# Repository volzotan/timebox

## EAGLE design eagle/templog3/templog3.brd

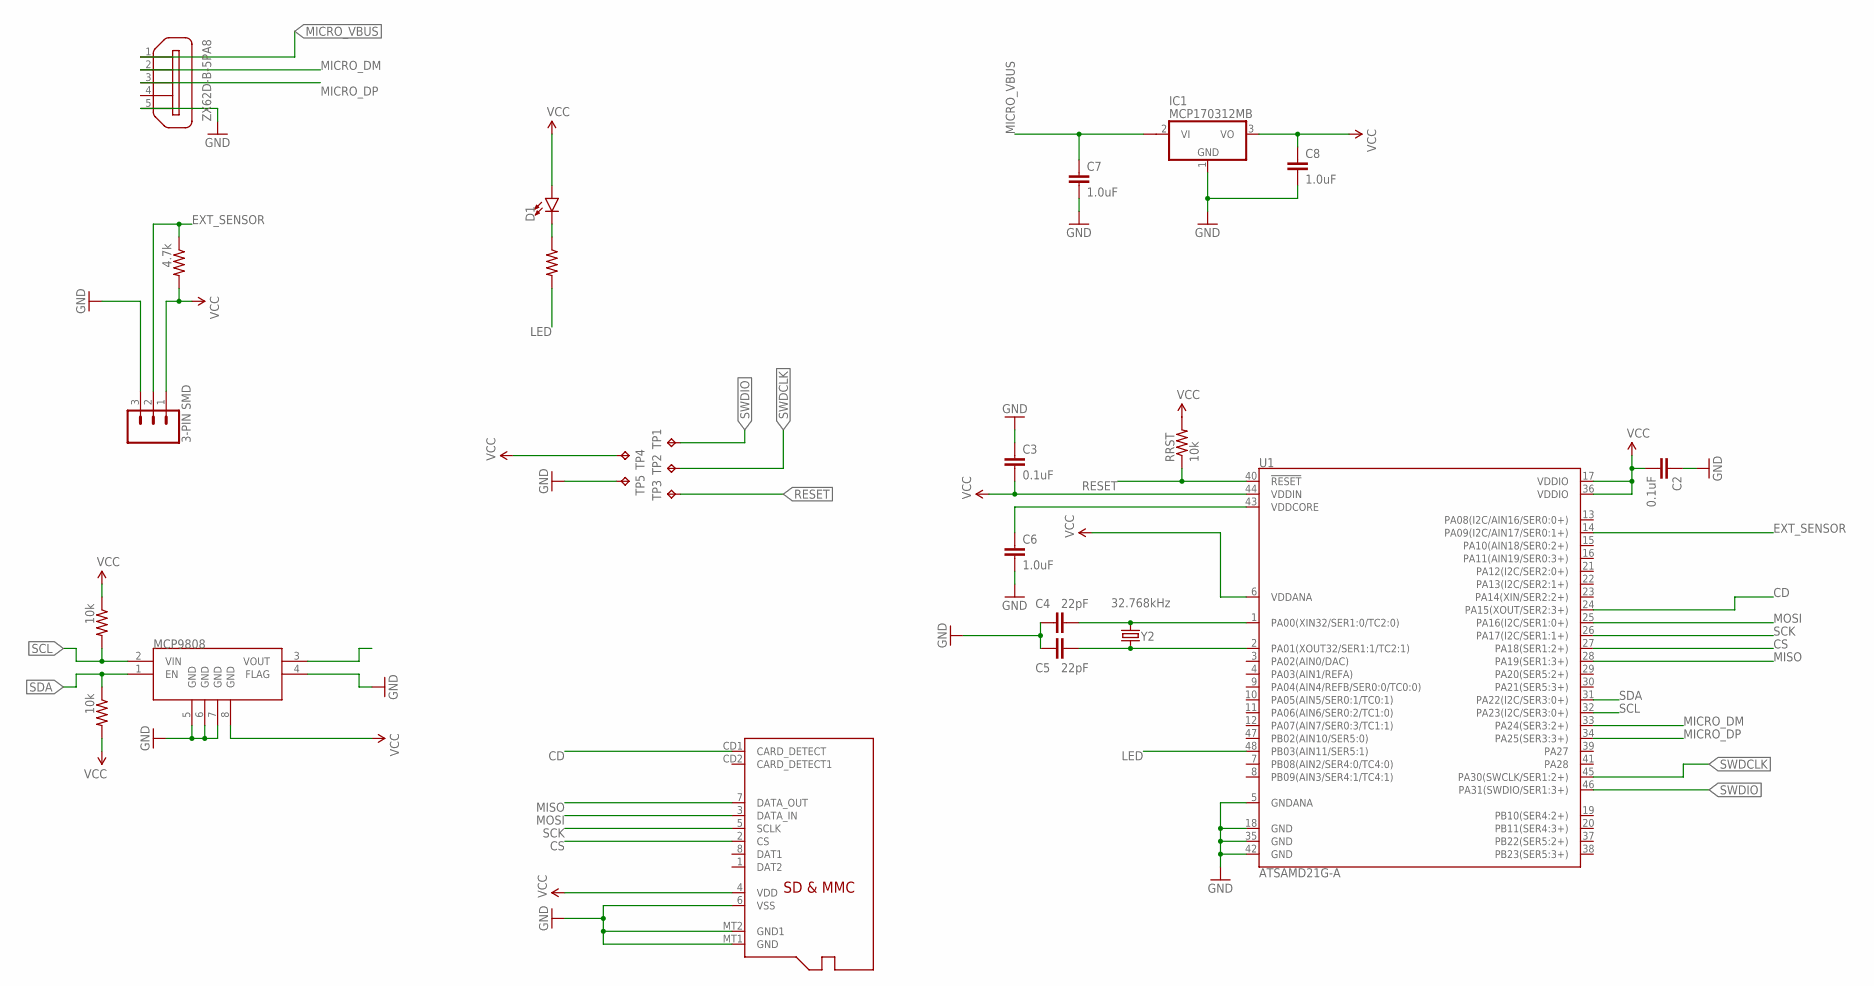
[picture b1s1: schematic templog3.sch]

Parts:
C2, C3: 0.1uF; 0805
C4, C5: 22pF; 0805
C6, C7, C8: 1.0uF; 0805
D1: LED1206; LED-1206
IC1: MCP170312MB; SOT89
J2: 3-PIN SMD; JST-3-SMD
MCP9808: V_REG_MIC5216; MSOP8
RRST: 10k; 0805
R_I2C_1, R_I2C_2: 10k; 0805
R_I2C_3: 4.7k; 0805
R_I2C_4: RESISTOR0805-RES; 0805
TP1, TP2, TP3, TP4, TP5: TPB1,27; B1,27
U1: ATSAMD21G-A; TQFP-48
U$1: MICROSD
X2: ZX62D-B-5PA8
Y2: 32.768kHz; CRYSTAL-SMD-3.2X1.5MM

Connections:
CD: U1.24 (PA15(XOUT/SER2:3+)), U$1.CD1 (CARD_DETECT)
CS: U1.27 (PA18(SER1:2+)), U$1.2 (CS)
EXT_SENSOR: J2.2, R_I2C_3.1, U1.14 (PA09(I2C/AIN17/SER0:1+))
GND: C2.1, C3.1, C4.1, C5.1, C6.2, C7.2, C8.2, IC1.1 (GND), J2.3, MCP9808.4 (FLAG), MCP9808.5 (GND), MCP9808.6 (GND), MCP9808.7 (GND), TP5.TP, U1.5 (GNDANA), U1.18 (GND), U1.35 (GND), U1.42 (GND), U$1.6 (VSS), U$1.MT1 (GND), U$1.MT2 (GND1), X2.5
LED: R_I2C_4.2, U1.48 (PB03(AIN11/SER5:1))
MICRO_DM: U1.33 (PA24(SER3:2+)), X2.2
MICRO_DP: U1.34 (PA25(SER3:3+)), X2.3
MICRO_VBUS: C7.1, IC1.2@1 (VI1), X2.1
MISO: U1.28 (PA19(SER1:3+)), U$1.7 (DATA_OUT)
MOSI: U1.25 (PA16(I2C/SER1:0+)), U$1.3 (DATA_IN)
unnamed: C6.1, U1.43 (VDDCORE)
unnamed: D1.C, R_I2C_4.1
unnamed: C4.2, U1.1 (PA00(XIN32/SER1:0/TC2:0)), Y2.P$2 (2)
unnamed: C5.2, U1.2 (PA01(XOUT32/SER1:1/TC2:1)), Y2.P$1 (1)
RESET: RRST.1, TP3.TP, U1.40 (!RESET!)
SCK: U1.26 (PA17(I2C/SER1:1+)), U$1.5 (SCLK)
SCL: MCP9808.2 (VIN), R_I2C_1.2, U1.32 (PA23(I2C/SER3:0+))
SDA: MCP9808.1 (EN), R_I2C_2.1, U1.31 (PA22(I2C/SER3:0+))
SWDCLK: TP2.TP, U1.45 (PA30(SWCLK/SER1:2+))
SWDIO: TP1.TP, U1.46 (PA31(SWDIO/SER1:3+))
VCC: C2.2, C3.2, C8.1, D1.A, IC1.3 (VO), J2.1, MCP9808.8 (GND), RRST.2, R_I2C_1.1, R_I2C_2.2, R_I2C_3.2, TP4.TP, U1.6 (VDDANA), U1.17 (VDDIO), U1.36 (VDDIO), U1.44 (VDDIN), U$1.4 (VDD)

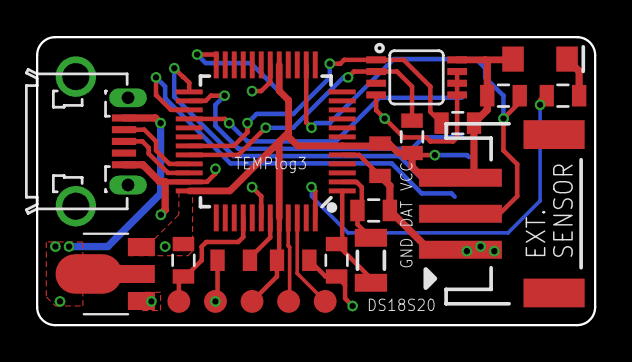
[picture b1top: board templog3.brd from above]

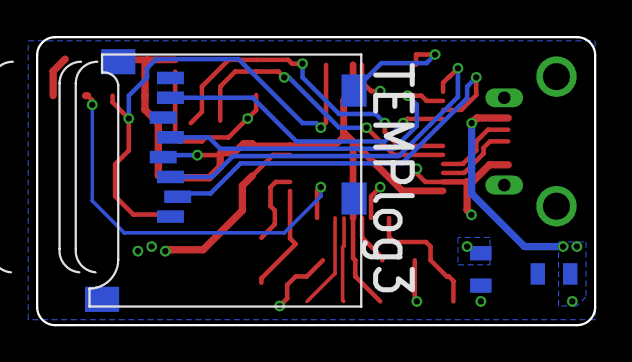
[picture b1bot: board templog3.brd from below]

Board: 2 copper layers, 31.0 x 16.0 mm, 25 parts (3 on the bottom side), 21 nets.

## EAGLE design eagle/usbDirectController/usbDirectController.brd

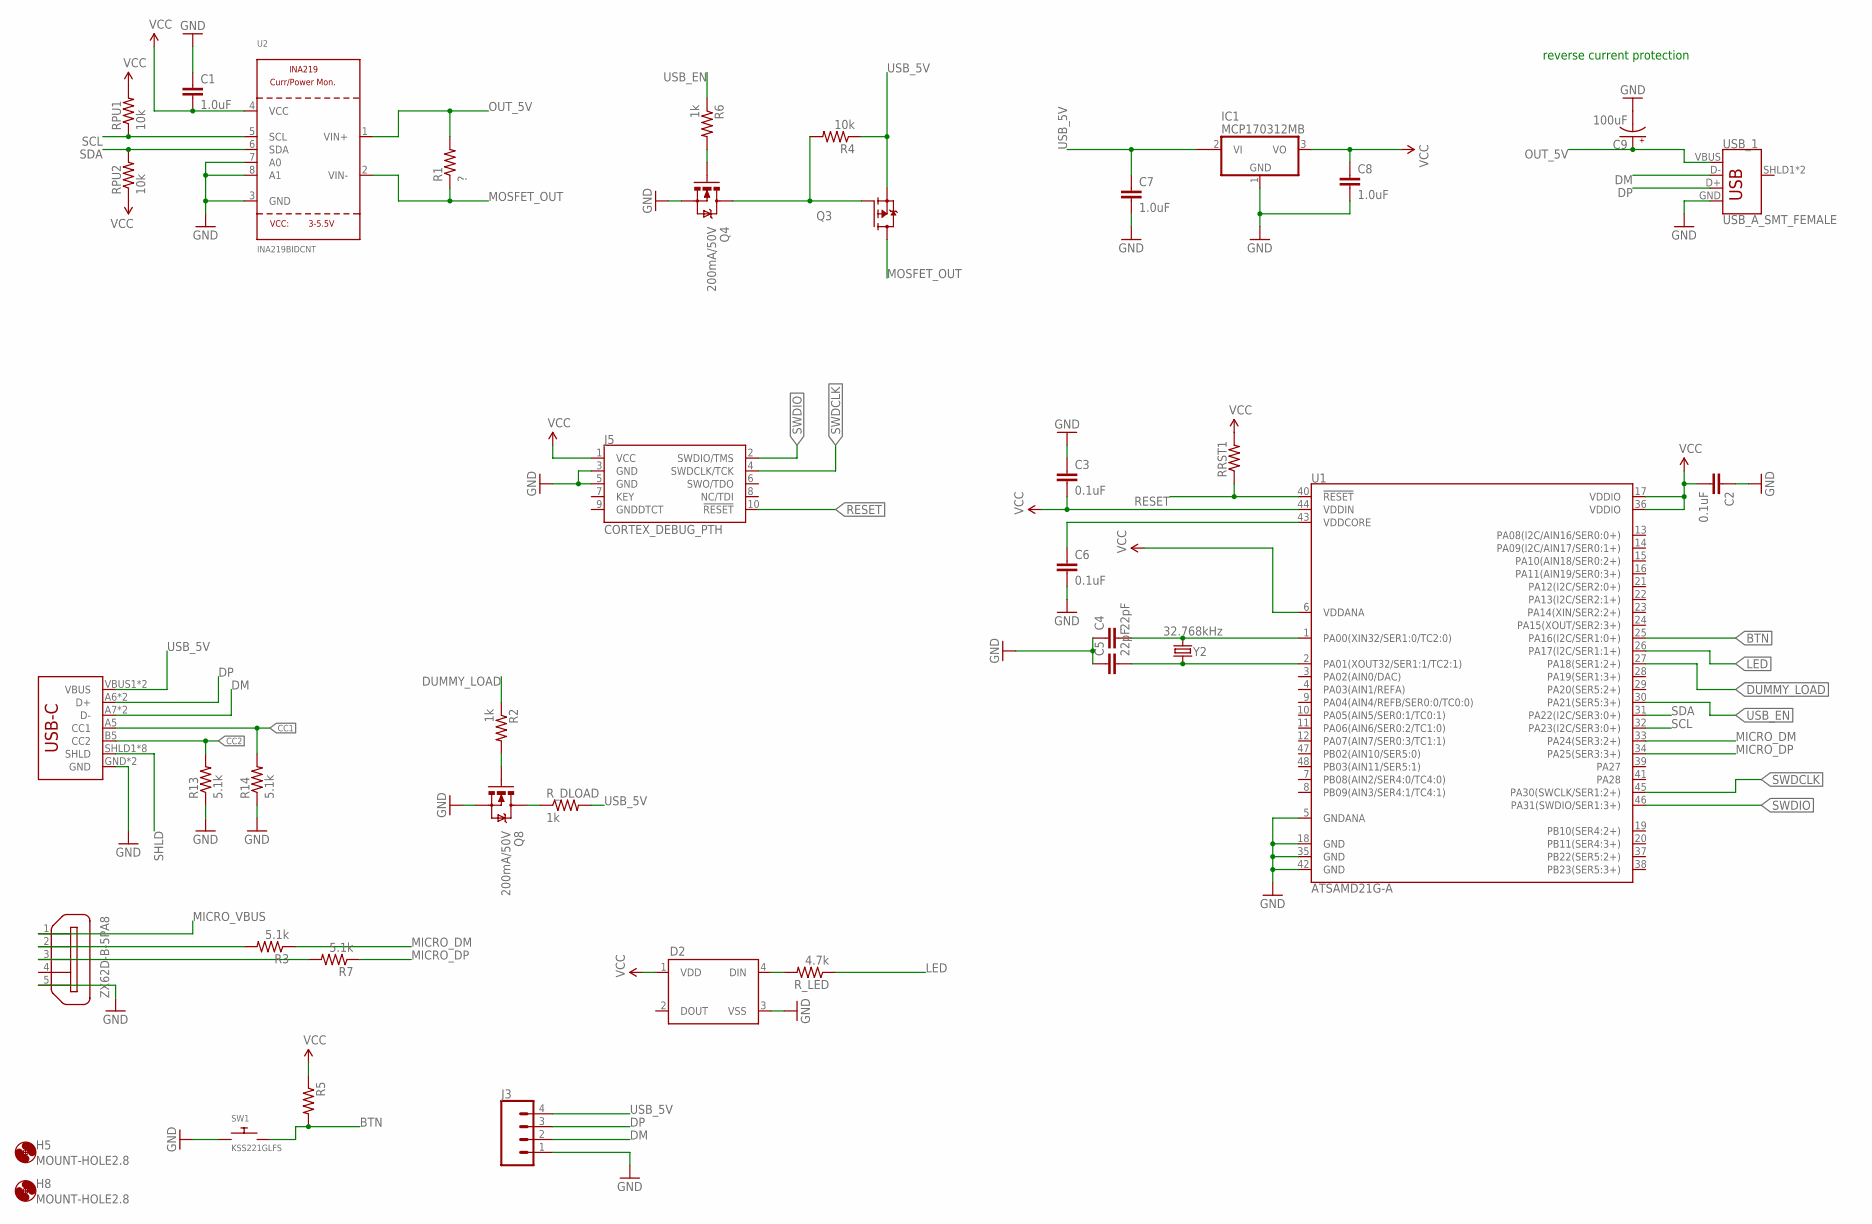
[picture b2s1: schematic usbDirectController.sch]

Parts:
C1, C7, C8: 1.0uF; 0805
C2, C3, C6: 0.1uF; 0805
C4, C5: 22pF; 0805
C9: 100uF; PANASONIC_D
D2: WS2812B
H5, H8: MOUNT-HOLE2.8; 2,8
IC1: MCP170312MB; SOT89
J1: USB_C16PIN; USB-C-16P
J3: CONN_04; 1X04
J5: CORTEX_DEBUG_PTH; 2X5-PTH-1.27MM
Q3: FDD4141TO252; TO252
Q4, Q8: 200mA/50V; SOT23-3
R1: ?; R2010
R2, R6: 1k; 0805
R3, R7, R13, R14: 5.1k; 0805
R4: 10k; 0805
R5: RESISTOR0805-RES; 0805
RPU1, RPU2: 10k; 0805
RRST1: RESISTOR0805-RES; 0805
R_DLOAD: 1k; 1206
R_LED: 4.7k; 0805
SW1: KSS221GLFS; BTN_CK_KSS
U1: ATSAMD21G-A; TQFP-48
U2: INA219BIDCNT; SOT23-8
USB_1: USB_A_SMT_FEMALE; USB-A-S-SILK-FEMALE
X2: ZX62D-B-5PA8
Y2: 32.768kHz; CRYSTAL-SMD-3.2X1.5MM

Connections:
BTN: R5.2, SW1.P$2, U1.25 (PA16(I2C/SER1:0+))
CC1: J1.A5 (CC1), R14.2
CC2: J1.B5 (CC2), R13.2
DM: J1.A7 (D-), J1.B7 (D-), J3.2, USB_1.D-
DP: J1.A6 (D+), J1.B6 (D+), J3.3, USB_1.D+
DUMMY_LOAD: R2.1, U1.27 (PA18(SER1:2+))
GND: C1.1, C2.1, C3.1, C4.1, C5.1, C6.2, C7.2, C8.2, C9.-, D2.3 (VSS), IC1.1 (GND), J1.GND, J1.GND2 (GND), J3.1, J5.3 (GND), J5.5 (GND), Q4.2 (S), Q8.2 (S), R13.1, R14.1, SW1.P$1, U1.5 (GNDANA), U1.18 (GND), U1.35 (GND), U1.42 (GND), U2.3 (GND), U2.7 (A0), U2.8 (A1), USB_1.GND, X2.5
LED: R_LED.1, U1.26 (PA17(I2C/SER1:1+))
MICRO_DM: R3.1, U1.33 (PA24(SER3:2+))
MICRO_DP: R7.1, U1.34 (PA25(SER3:3+))
MICRO_VBUS: X2.1
MOSFET_OUT: Q3.3 (D), R1.1, U2.2 (VIN-)
unnamed: C6.1, U1.43 (VDDCORE)
unnamed: Q4.1 (G), R6.2
unnamed: Q3.1 (G), Q4.3 (D), R4.2
unnamed: R3.2, X2.2
unnamed: D2.4 (DIN), R_LED.2
unnamed: C4.2, U1.1 (PA00(XIN32/SER1:0/TC2:0)), Y2.P$2 (2)
unnamed: R7.2, X2.3
unnamed: Q8.1 (G), R2.2
unnamed: Q8.3 (D), R_DLOAD.1
unnamed: C5.2, U1.2 (PA01(XOUT32/SER1:1/TC2:1)), Y2.P$1 (1)
OUT_5V: C9.+, R1.2, U2.1 (VIN+), USB_1.VBUS
RESET: J5.10 (!RESET), RRST1.1, U1.40 (!RESET!)
SCL: RPU1.1, U1.32 (PA23(I2C/SER3:0+)), U2.5 (SCL)
SDA: RPU2.2, U1.31 (PA22(I2C/SER3:0+)), U2.6 (SDA)
SHLD: J1.SHLD1 (SHLD), J1.SHLD2 (SHLD), J1.SHLD3 (SHLD), J1.SHLD4 (SHLD), J1.SHLD5 (SHLD), J1.SHLD6 (SHLD), J1.SHLD7 (SHLD), J1.SHLD8 (SHLD)
SWDCLK: J5.4 (SWDCLK/TCK), U1.45 (PA30(SWCLK/SER1:2+))
SWDIO: J5.2 (SWDIO/TMS), U1.46 (PA31(SWDIO/SER1:3+))
USB_5V: C7.1, IC1.2@1 (VI1), J1.VBUS1 (VBUS), J1.VBUS2 (VBUS), J3.4, Q3.2 (S), R4.1, R_DLOAD.2
USB_EN: R6.1, U1.30 (PA21(SER5:3+))
VCC: C1.2, C2.2, C3.2, C8.1, D2.1 (VDD), IC1.3 (VO), J5.1 (VCC), R5.1, RPU1.2, RPU2.1, RRST1.2, U1.6 (VDDANA), U1.17 (VDDIO), U1.36 (VDDIO), U1.44 (VDDIN), U2.4 (VCC)

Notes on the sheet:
reverse current protection

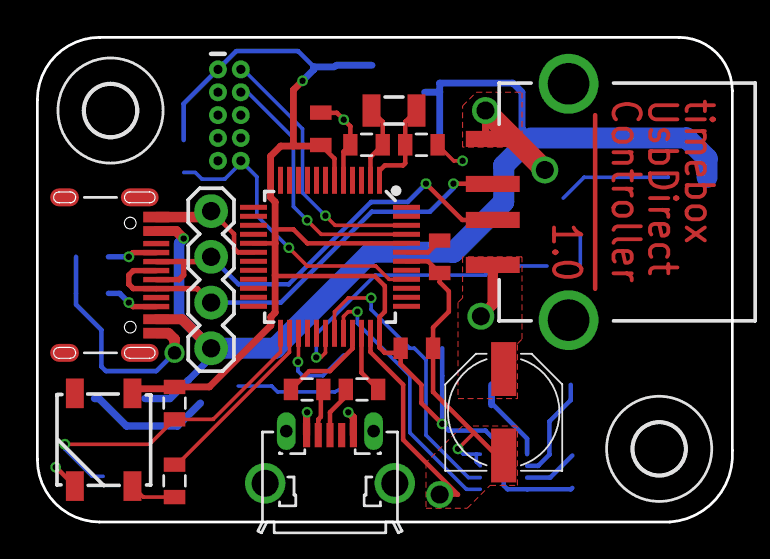
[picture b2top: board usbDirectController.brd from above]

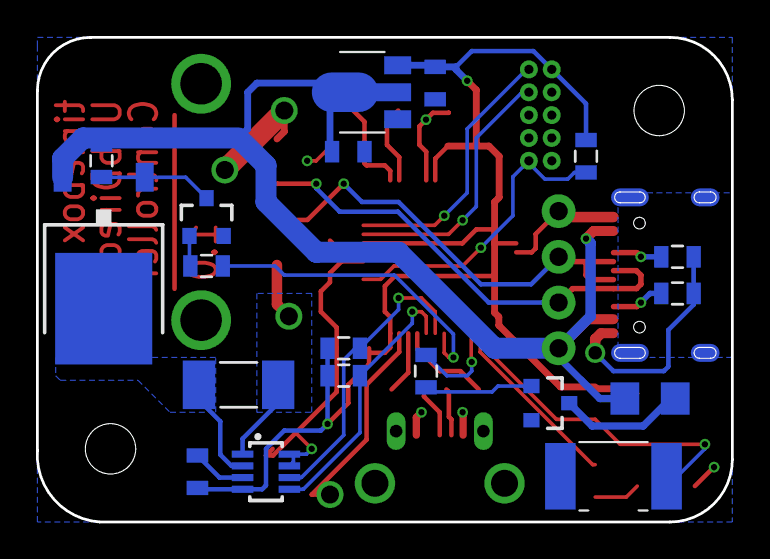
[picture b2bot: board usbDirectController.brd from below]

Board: 2 copper layers, 38.6 x 26.9 mm, 39 parts (19 on the bottom side), 31 nets.

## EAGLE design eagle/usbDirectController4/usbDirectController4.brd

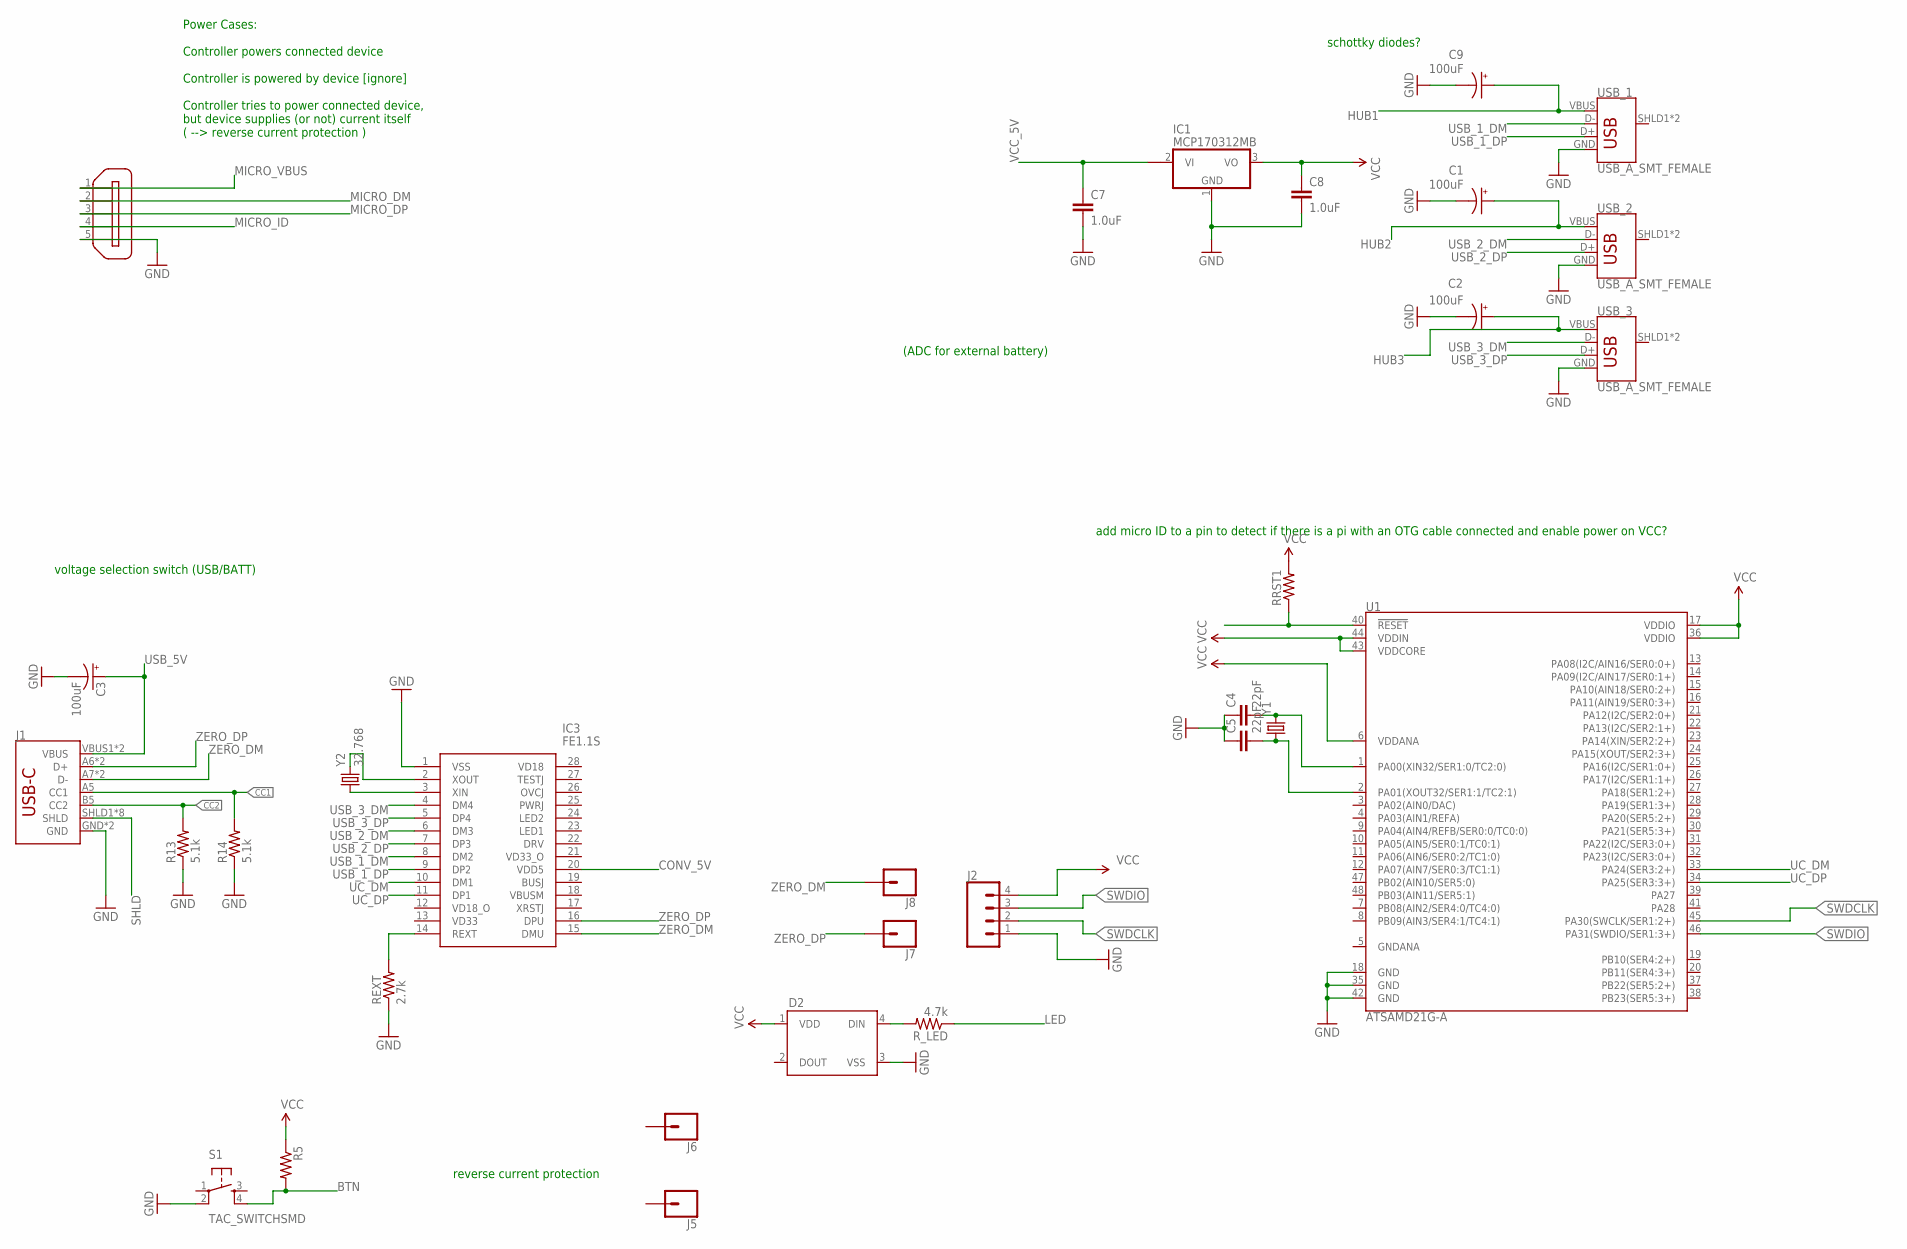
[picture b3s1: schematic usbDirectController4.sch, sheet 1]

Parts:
C1, C2, C3, C9: 100uF; PANASONIC_D
C4, C5: 22pF; 1206
C7, C8: 1.0uF; 1206
D2: WS2812B
IC1: MCP170312MB; SOT89
IC3: FE1.1S; SOP64P600X175-28N
J1: USB_C16PIN; USB-C-16P
J2: CONN_04; 1X04
J5, J6, J7, J8: CONN_01POGOPIN_HOLE_0.58; 1X01_POGOPIN_HOLE_0.58_DIA
R5: RESISTOR1206; 1206
R13, R14: 5.1k; 0805
REXT: 2.7k; 1206
RRST1: RESISTOR1206; 1206
R_LED: 4.7k; 1206
S1: TAC_SWITCHSMD; TACTILE-PTH
U1: ATSAMD21G-A; TQFP-48
USB_1, USB_2, USB_3: USB_A_SMT_FEMALE; USB-A-S-SILK-FEMALE
X2: ZX62D-B-5PA8
Y1: CRYSTALCRYSTAL-SMD-5X3-16MHZ; CRYSTAL-SMD-5X3
Y2: 32.768; CRYSTAL-SMD-5X3

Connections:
BTN: R5.2, S1.4
CC1: J1.A5 (CC1), R14.2
CC2: J1.B5 (CC2), R13.2
CONV_5V: IC3.20 (VDD5)
GND: C1.-, C2.-, C3.-, C4.1, C5.1, C7.2, C8.2, C9.-, D2.3 (VSS), IC1.1 (GND), IC3.1 (VSS), J1.GND, J1.GND2 (GND), J2.1, R13.1, R14.1, REXT.1, S1.2, U1.18 (GND), U1.35 (GND), U1.42 (GND), USB_1.GND, USB_2.GND, USB_3.GND, X2.5; also elsewhere on the board
HUB1: C9.+, USB_1.VBUS
HUB2: C1.+, USB_2.VBUS
HUB3: C2.+, USB_3.VBUS
LED: R_LED.1
MICRO_DM: X2.2
MICRO_DP: X2.3
MICRO_ID: X2.4
MICRO_VBUS: X2.1
unnamed: D2.4 (DIN), R_LED.2
unnamed: C4.2, U1.1 (PA00(XIN32/SER1:0/TC2:0)), Y1.3 (2)
unnamed: RRST1.1, U1.40 (!RESET!)
unnamed: IC3.3 (XIN), Y2.1
unnamed: IC3.2 (XOUT), Y2.3 (2)
unnamed: IC3.14 (REXT), REXT.2
unnamed: C5.2, U1.2 (PA01(XOUT32/SER1:1/TC2:1)), Y1.1
SHLD: J1.SHLD1 (SHLD), J1.SHLD2 (SHLD), J1.SHLD3 (SHLD), J1.SHLD4 (SHLD), J1.SHLD5 (SHLD), J1.SHLD6 (SHLD), J1.SHLD7 (SHLD), J1.SHLD8 (SHLD)
SWDCLK: J2.2, U1.45 (PA30(SWCLK/SER1:2+))
SWDIO: J2.3, U1.46 (PA31(SWDIO/SER1:3+))
UC_DM: IC3.10 (DM1), U1.33 (PA24(SER3:2+))
UC_DP: IC3.11 (DP1), U1.34 (PA25(SER3:3+))
USB_1_DM: IC3.8 (DM2), USB_1.D-
USB_1_DP: IC3.9 (DP2), USB_1.D+
USB_2_DM: IC3.6 (DM3), USB_2.D-
USB_2_DP: IC3.7 (DP3), USB_2.D+
USB_3_DM: IC3.4 (DM4), USB_3.D-
USB_3_DP: IC3.5 (DP4), USB_3.D+
USB_5V: C3.+, J1.VBUS1 (VBUS), J1.VBUS2 (VBUS)
VCC: C8.1, D2.1 (VDD), IC1.3 (VO), J2.4, R5.1, RRST1.2, U1.6 (VDDANA), U1.17 (VDDIO), U1.36 (VDDIO), U1.43 (VDDCORE), U1.44 (VDDIN)
VCC_5V: C7.1, IC1.2@1 (VI1); also elsewhere on the board
ZERO_DM: IC3.15 (DMU), J1.A7 (D-), J1.B7 (D-), J8.1
ZERO_DP: IC3.16 (DPU), J1.A6 (D+), J1.B6 (D+), J7.1

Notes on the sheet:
(ADC for external battery)
schottky diodes?
voltage selection switch (USB/BATT)
reverse current protection
add micro ID to a pin to detect if there is a pi with an OTG cable connected and enable power on VCC?
Power Cases: Controller powers connected device Controller is powered by device [ignore] Controller tries to power connected device, but device supplies (or not) current itself ( --> reverse current protection )

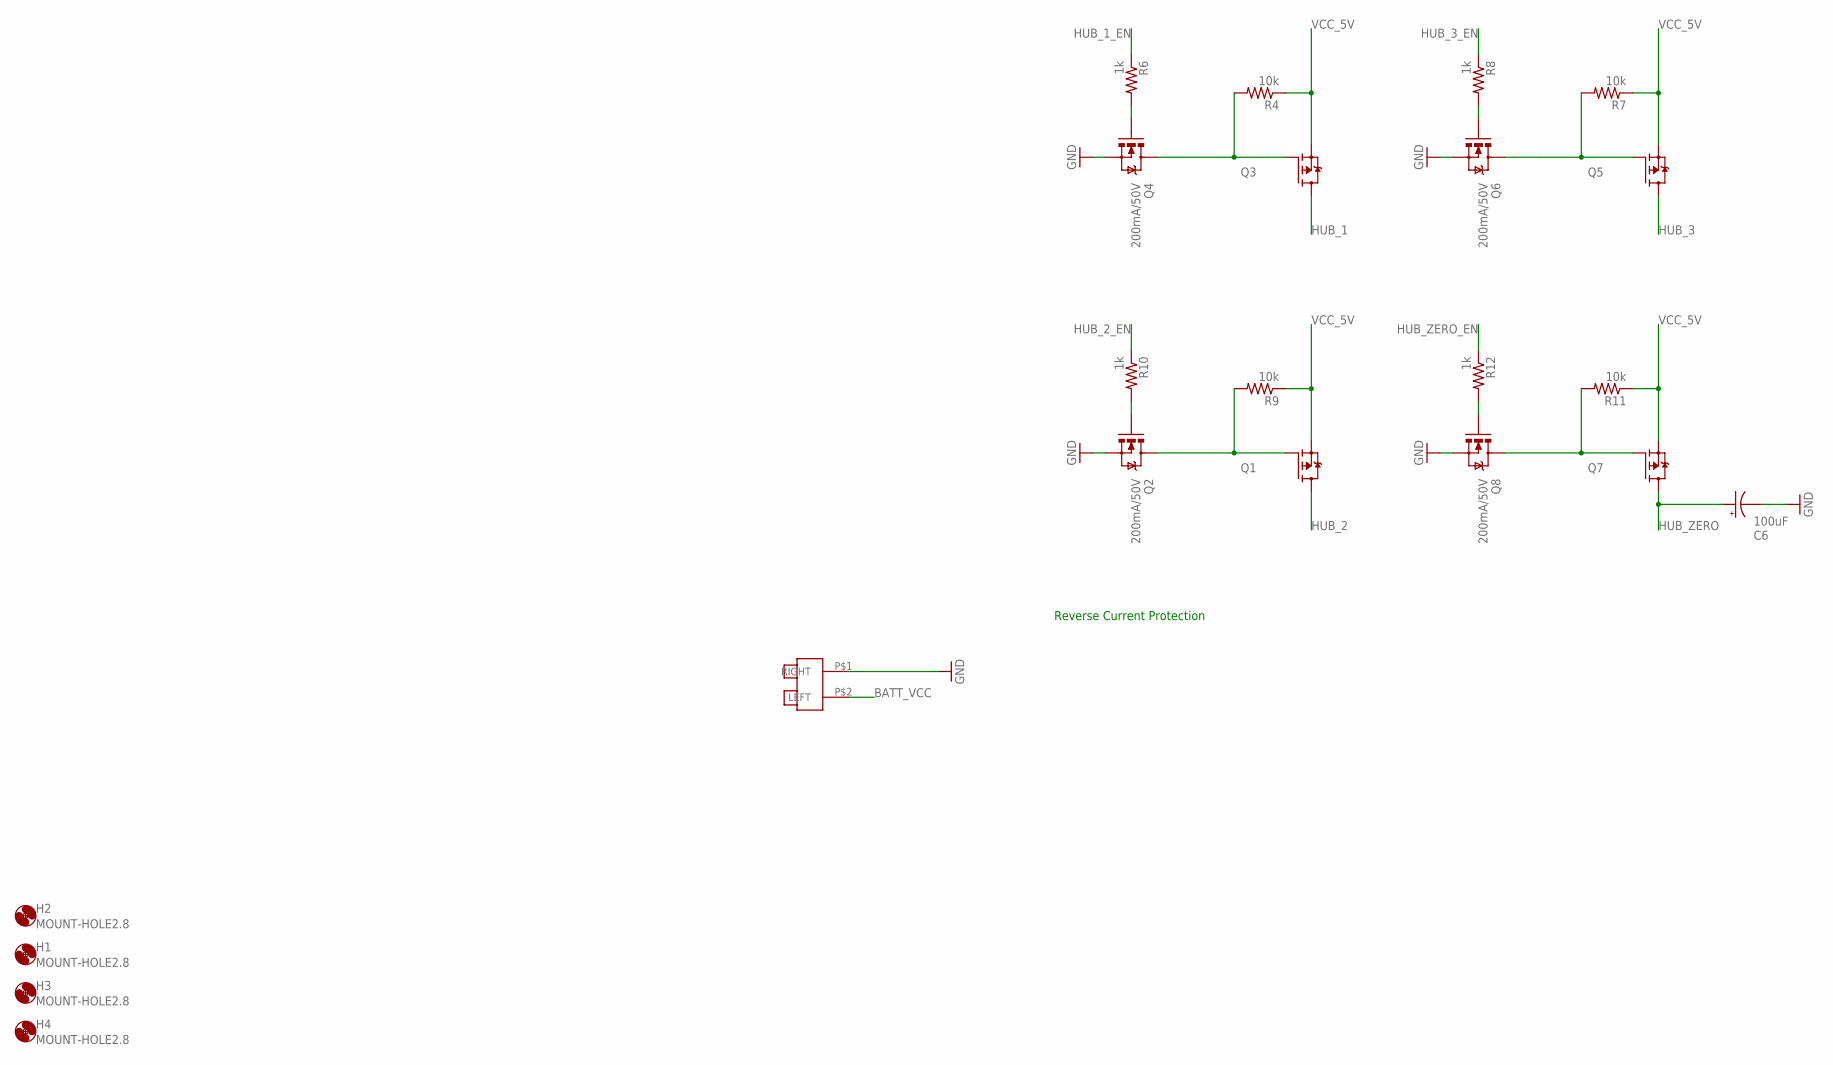
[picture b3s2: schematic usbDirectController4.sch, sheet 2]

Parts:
C6: 100uF; PANASONIC_D
H1, H2, H3, H4: MOUNT-HOLE2.8; 2,8
Q1, Q3, Q5, Q7: FDD4141TO252; TO252
Q2, Q4, Q6, Q8: 200mA/50V; SOT23-3
R4, R7, R9, R11: 10k; 1206
R6, R8, R10, R12: 1k; 1206
U$4: NANOFIT2

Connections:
BATT_VCC: U$4.P$2 (LEFT)
GND: C6.-, Q2.2 (S), Q4.2 (S), Q6.2 (S), Q8.2 (S), U$4.P$1 (RIGHT); also elsewhere on the board
HUB_1: Q3.3 (D)
HUB_1_EN: R6.1
HUB_2: Q1.3 (D)
HUB_2_EN: R10.1
HUB_3: Q5.3 (D)
HUB_3_EN: R8.1
HUB_ZERO: C6.+, Q7.3 (D)
HUB_ZERO_EN: R12.1
unnamed: Q1.1 (G), Q2.3 (D), R9.2
unnamed: Q4.1 (G), R6.2
unnamed: Q3.1 (G), Q4.3 (D), R4.2
unnamed: Q2.1 (G), R10.2
unnamed: Q5.1 (G), Q6.3 (D), R7.2
unnamed: Q6.1 (G), R8.2
unnamed: Q7.1 (G), Q8.3 (D), R11.2
unnamed: Q8.1 (G), R12.2
VCC_5V: Q1.2 (S), Q3.2 (S), Q5.2 (S), Q7.2 (S), R4.1, R7.1, R9.1, R11.1; also elsewhere on the board

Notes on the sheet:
Reverse Current Protection

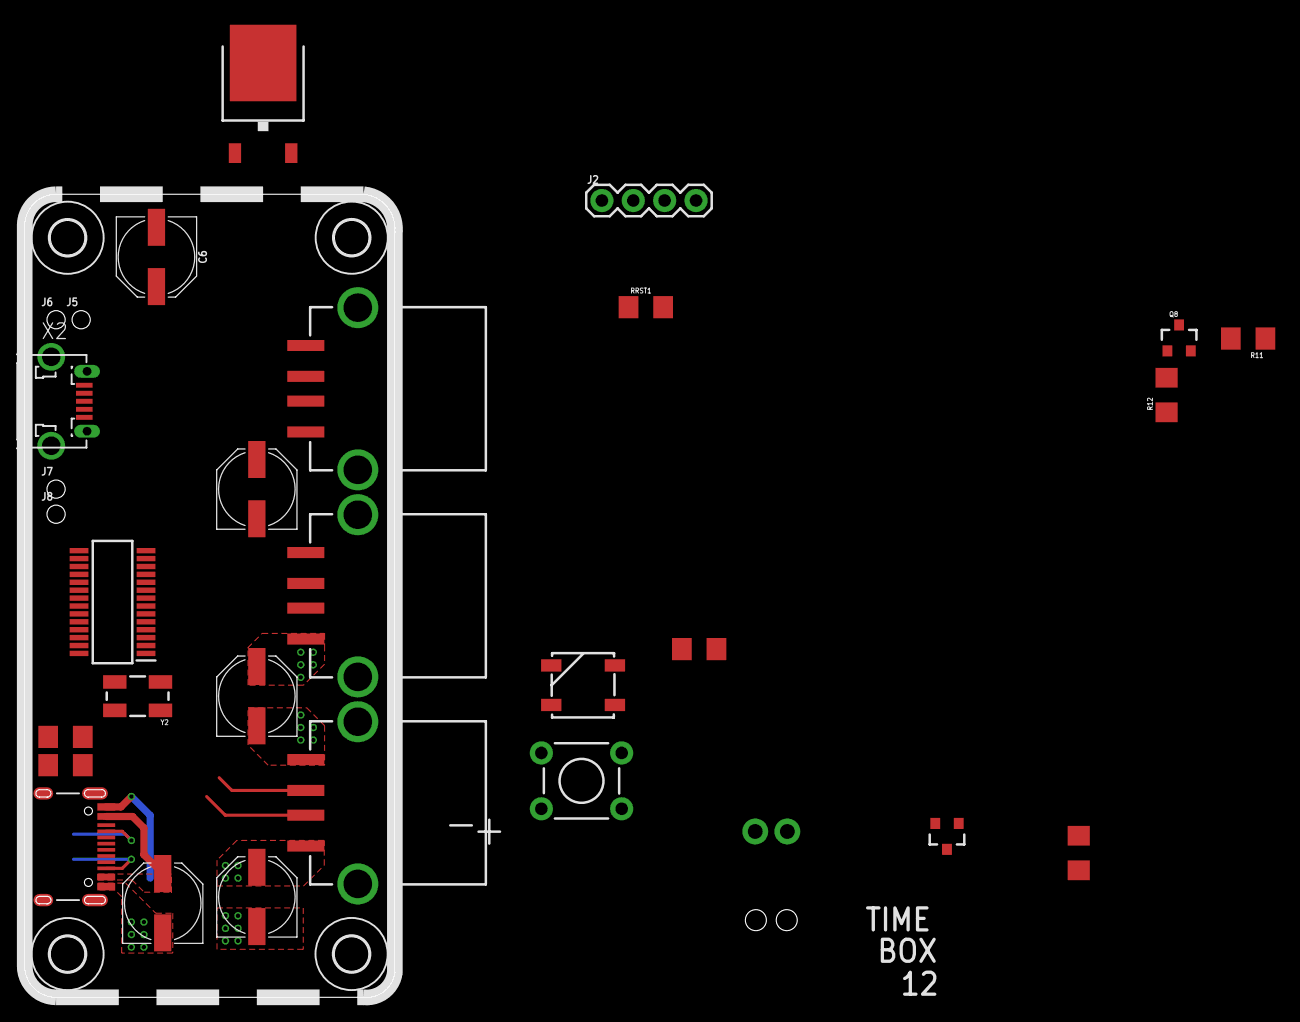
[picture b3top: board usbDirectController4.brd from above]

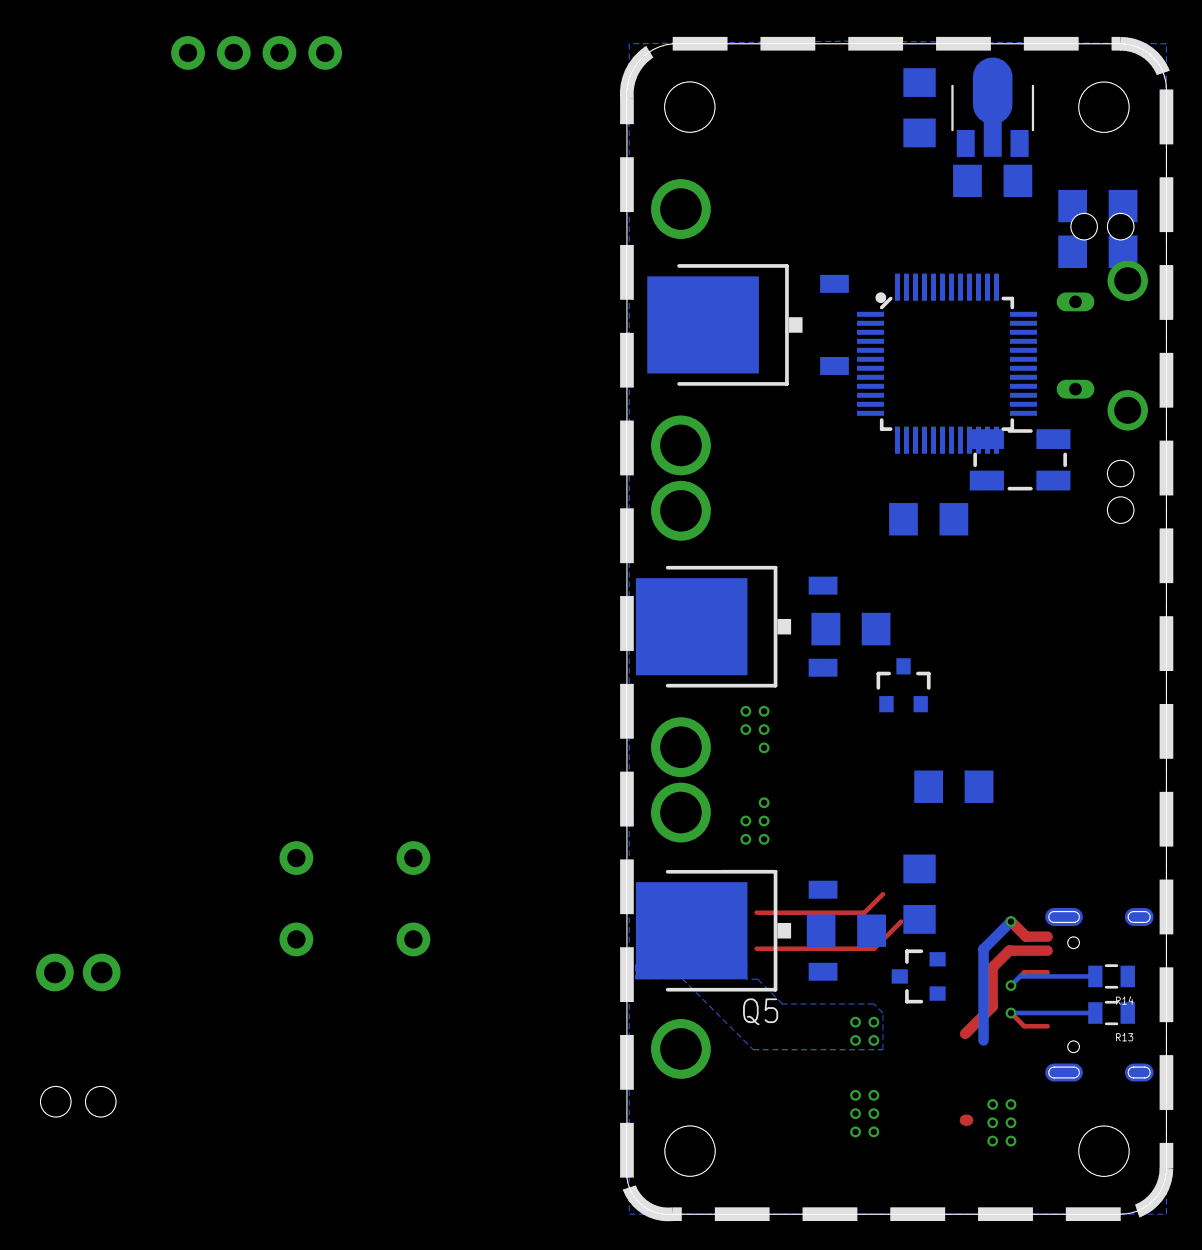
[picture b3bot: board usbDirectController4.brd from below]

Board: 2 copper layers, 30.0 x 65.0 mm, 53 parts (19 on the bottom side), 39 nets.

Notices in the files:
parts and their libraries:
SparkFun-Passives: Licensing: Creative Commons ShareAlike 4.0 International - https://creativecommons.org/licenses/by-sa/4.0
